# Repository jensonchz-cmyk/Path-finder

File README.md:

I added another button and LED to make it more original and uploaded a bom file
<br>

<br>
This is my Pathfinder project, I created this as it looked cool to make, I followed a tutorial from the stasis started projects.
My project is a pathfinder that has three buttons a XIAO microcontroller and three LEDS, the purpose of this was to have fun and having a good experience. One of my functions was that if you click the buttons in the right order one of the lights turns on and for three times
<br>

<br>

This is my schematic, after this I moved onto the PCB
<br>

<br>

Then I mapped the footprints.
<br>

<br>

This is my PCB schematic.
<br>

<br>

This is my 3D model.
<br>

BOM
<br>

1.42 dollars - Keycaps - To cover the switches

https://www.aliexpress.com/item/1005007791365492.html?spm=a2g0o.cart.0.0.6b9638daSATGTK&mp=1&pdp_npi=6%40dis%21AUD%21AUD+9.53%21AUD+1.45%21%21AUD+1.45%21%21%21%402101d6fe17822926031567990eea66%2112000042214863584%21ct%21AU%217797925100%21%211%210%21
<br>

1.42 dollars - Switches - To function as inputs

https://www.aliexpress.com/item/1005006217630409.html?spm=a2g0o.cart.0.0.6b9638daSATGTK&mp=1&pdp_npi=6%40dis%21AUD%21AUD+7.96%21AUD+1.45%21%21AUD+1.45%21%21%21%402101d6fe17822926031567990eea66%2112000036325155647%21ct%21AU%217797925100%21%211%210%21
<br>

0.97 dollars - LEDS - To light up

https://www.aliexpress.com/item/1005011964189969.html?spm=a2g0o.cart.0.0.6b9638daSATGTK&mp=1&pdp_npi=6%40dis%21AUD%21AUD+1.07%21AUD+1.07%21%21AUD+1.07%21%21%21%402101d6fe17822926031567990eea66%2112000057145223850%21ct%21AU%217797925100%21%211%210%21
<br>

7.60 dollars - Xiao - To run the programs.

https://www.aliexpress.com/item/1005008200917480.html?spm=a2g0o.cart.0.0.6b9638daSATGTK&mp=1&pdp_npi=6%40dis%21AUD%21AUD+11.12%21AUD+7.89%21%21AUD+7.89%21%21%21%402101d6fe17822926031567990eea66%2112000058130698585%21ct%21AU%217797925100%21%211%210%21
<br>

0.76 dollars - Resistors (100ohm) - To make sure the LEDS don't blow

](https://www.aliexpress.com/item/1005006040209297.html?spm=a2g0o.cart.0.0.515938daQjPjzf&mp=1&pdp_npi=6%40dis%21AUD%21AUD%200.76%21AUD%200.76%21%21AUD%200.76%21%21%21%402101d6ff17822933622073493ebdb0%2112000035442807620%21ct%21AU%217797925100%21%211%210%21&pdp_ext_f=%7B%22cart2PdpParams%22%3A%7B%22pdpBusinessMode%22%3A%22retail%22%7D%7D)

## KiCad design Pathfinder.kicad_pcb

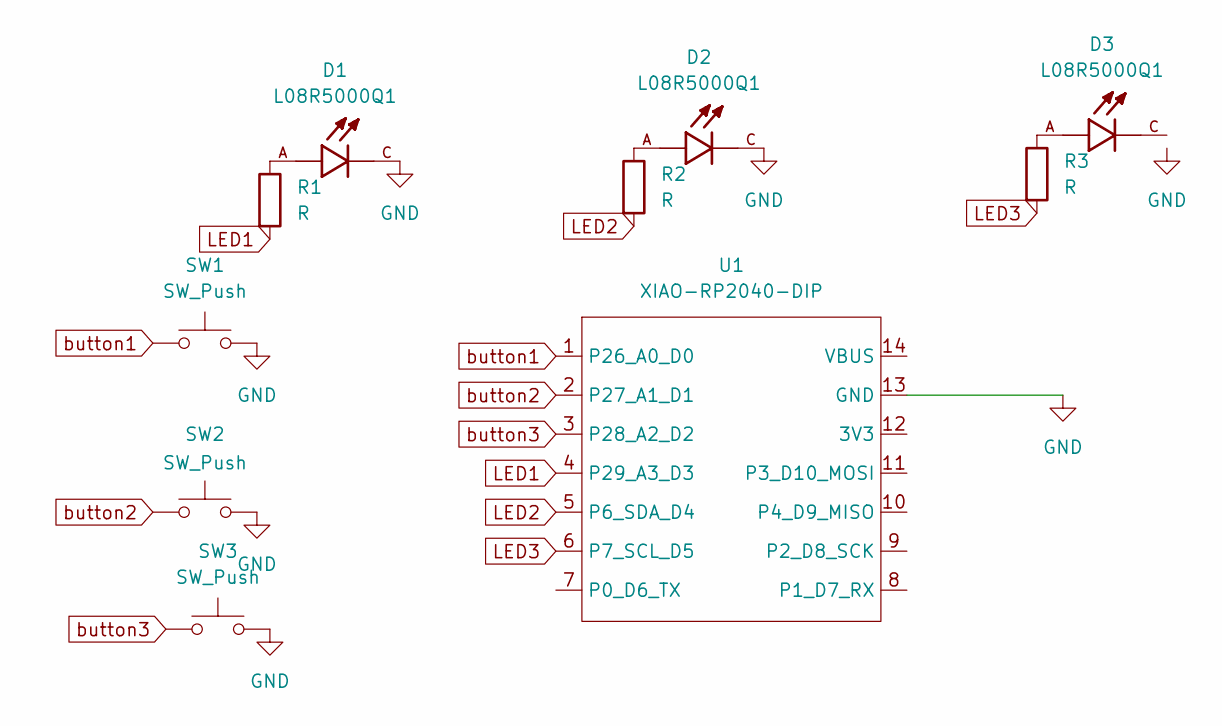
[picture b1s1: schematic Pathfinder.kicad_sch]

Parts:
D1, D2, D3: L08R5000Q1; LEDRD254W57D500H1070; PARTREV NA
R1, R2, R3: R; R_Axial_DIN0204_L3.6mm_D1.6mm_P5.08mm_Horizontal
SW1, SW2, SW3: SW_Push; SW_Cherry_MX_1.00u_PCB
U1: XIAO-RP2040-DIP; XIAO-RP2040-DIP (3)

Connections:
GND: D1.C, D2.C, SW1.2, SW2.2, SW3.2, U1.13 (GND)
LED1: R1.2, U1.4 (P29_A3_D3)
LED2: R2.2, U1.5 (P6_SDA_D4)
LED3: R3.2, U1.6 (P7_SCL_D5)
unnamed: D1.A, R1.1
unnamed: D2.A, R2.1
unnamed: D3.A, R3.1
button1: SW1.1, U1.1 (P26_A0_D0)
button2: SW2.1, U1.2 (P27_A1_D1)
button3: SW3.1, U1.3 (P28_A2_D2)

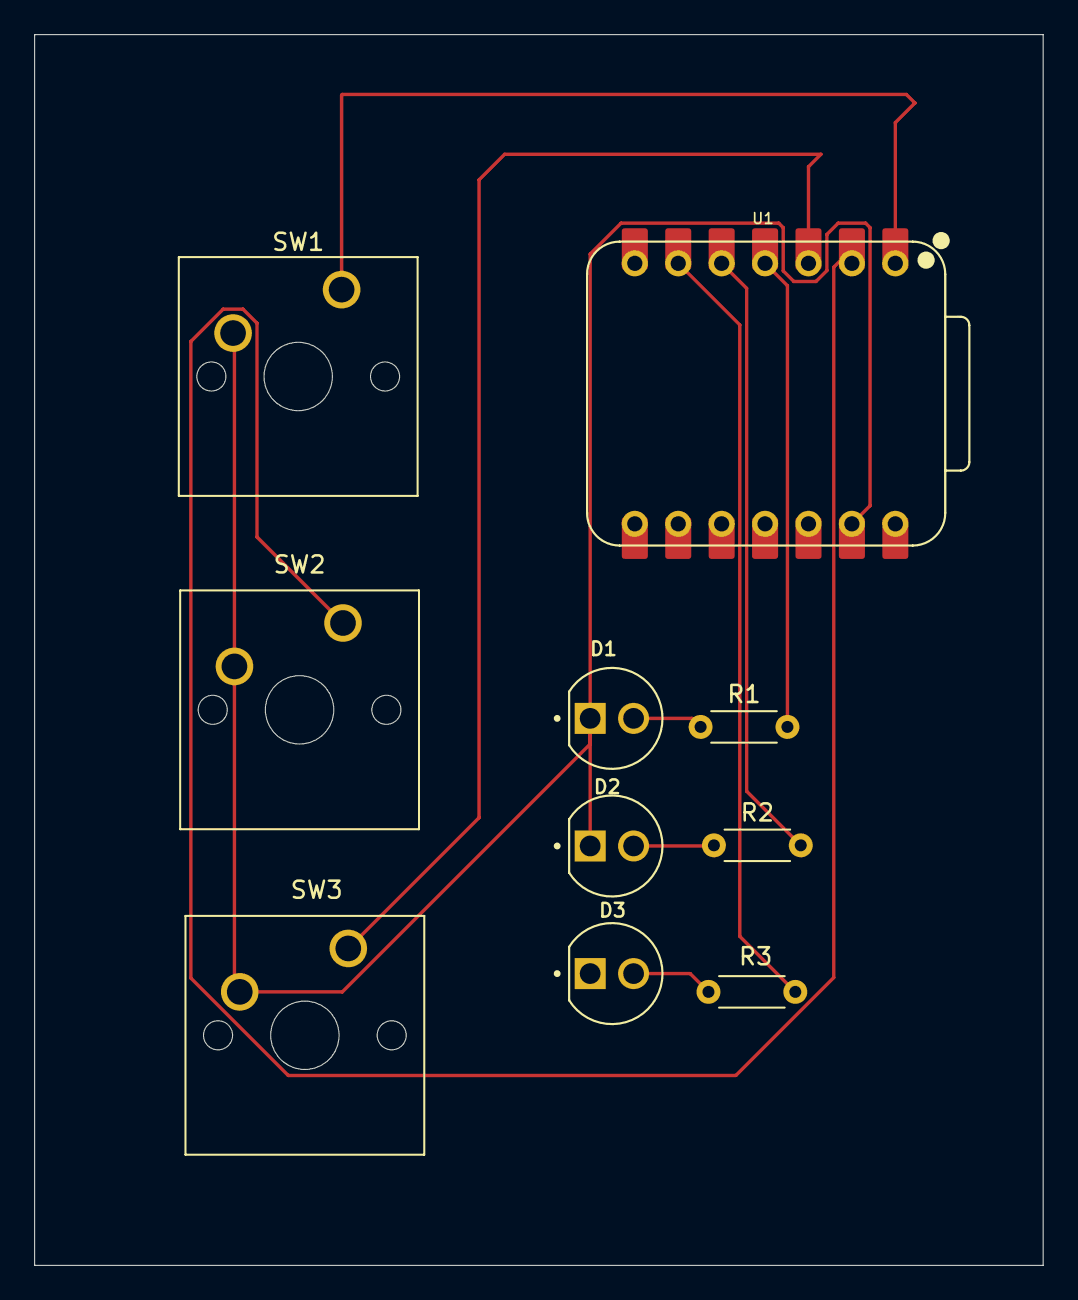
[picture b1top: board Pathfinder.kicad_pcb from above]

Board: 2 copper layers, 59.0 x 72.0 mm, 10 parts (0 on the bottom side), 10 nets.

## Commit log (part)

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2026-06-24 README.md
